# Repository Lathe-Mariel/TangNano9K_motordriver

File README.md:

# TangNano9K_Motordriver Board
  
Tang Nano 9K(Sipeed)用のマザーボード（拡張ボード）です．  
This is mother board for Tang Nano 9K(Sipeed).  

オープンソースの回路CADである，KiCAD のプロジェクトになっています．  
These files were made by KiCAD.
  
/doc ドキュメント用の素材  
/output　KiCADで出力したガーバーデータ  
/output/tangnano9k_motordriver-v3.zip　　PCBメーカにアップロードするファイル  
/sampleProject　この基板向けの数種類のサンプルプロジェクト  

## 機能 Functions
次の機能を実装できます．
- ステッピングモータドライバ x2ch <TB67S101ANG(TOSHIBA)>
- ロータリエンコーダ x2
- 8x8 マトリクスLED <OSL641501-BRA(Optsupply)>
- 7セグメントLED
- DIP Switch(8ch)

You can install these functions with this board.
- Stepper motor driver x2ch
- Rotary encoder x2
- 8x8 Matrix LED
- 7segment LED
- DIP Switch(8ch)

## 電源 Power supply
ボード上にDC-DCコンバータBP5293-50(ROHM)を実装できます．  
DC-DCコンバータには7～26Vを入力し，出力される5VをTang Nano 9Kへ供給できます．  
DC-DC converter can be installed on the board.  
  
基板上のDCジャックへ入力された電圧は，上記DC-DCコンバータとモータ・ドライバICのモータ電源（VM）へ入力されます．  
 
## FPGA側のピンを共用する機能 Multi purpose pins for board functions
　FPGAのピン数が限られているので，拡張ボードの持つ機能のうち，一部の機能は同時利用はできません．  
   
### HDMIコネクタとマトリクスLED＆ロータリ・エンコーダ×2
　DVI信号を出力する場合， `HDMI_CK_N(68)` ， `HDMI_CK_P(69)` ， `HDMI_D0` ～ `HDMI_D2` など8本の信号を使います．これらは，ロータリ・エンコーダ2ch目およびマトリクスLEDの信号と競合します．従ってDVI出力する場合は，ロータリ・エンコーダの2ch目とマトリクスLEDが使えません．  
  ボードにマトリクスLEDを実装するときは，必要に応じて脱着できるようにピンソケット経由にするのがお勧めです． 

### HDMIコネクタとマトリクスLED
　一部の信号を共有しています．HDMIコネクタから信号を出す場合はマトリクスLEDを取り付けない方がよいでしょう．  
 マトリクスLEDを実装するときは，ピンソケットを介して取り付けるのがお勧めです．そうすれば，マトリクスLEDを必要に応じて脱着できます．  
  
### 排他利用する機能の選択 Selection of exclusive functions
　モータドライバの励磁モード選択は `INA1` ， `INA2` ， `INB1` ， `INB2` 端子で行います．  
　2CH目（基板下側）のモータドライバは，ソルダジャンパ `JP1～JP4` をショートすると， `INA1～INB2` の全てがVCCに接続され，励磁モードが2相励磁に固定されます（この場合， `JP5～JP8` はオープンのままにする）．   
 　2ch目のモータドライバで1-2相励磁やW1-2相励磁を行いたい場合，ソルダジャンパ `JP5～JP8` をショートさせます．すると `INA1～INB2` がFPGAに接続されるので，FPGAからHi/Lowを制御できます．  
  　ちなみに1ch目のモータドライバについては，このようなソルダジャンパはありません． `INA1～INB2` は全てFPGAに直結されているので，どの様な励磁モードを使う場合でも，FPGAから制御する必要があります．  
  
  FPGA側では，これらの端子をロータリエンコーダの2ch目と共有しています．  
  従って，モータドライバの2ch目の1-2相励磁選択と，ロータリエンコーダの2ch目は排他利用となります．  
#### 設定例
　①例えば，モータドライバを1chしか使わない場合は， `JP1～JP8` のソルダジャンパをオープンのまま使用します（7セグLEDを使うなら `JP9` のみショートする）．  
 　②例えば，モータドライバの2ch目を1-2相励磁（あるいはW1-2相励磁）で使いたい場合は， `JP5～JP8` のソルダジャンパをショートします（ `INA1～INB2` がFPGAと直結される）．  
  この場合7セグLEDとロータリエンコーダの2ch目は使用できません（実装もしない方がよいでしょう）．  

- JP1 ～ JP4　　ショートさせるとINA1～INB2をTB67S101ANGのVCCピンと接続
- JP5 ～ JP8　　ショートさせるとFPGAとINA1～INB2を接続
- JP9　　JP5の線を7セグLEDのコモンに接続
- JP10 ～ JP17　　マトリクスLEDに（アノード側）電流制限抵抗を付けない場合は，これらのソルダージャンパをショートさせてください  

## マトリクスLED MatrixLED
　~増幅回路も電流制限抵抗も入れていません．~  
　~ワイルドだろぅ？~  
  電流制限抵抗を入れない場合は，ソルダージャンパ `JP10` ～ `JP17` をジャンパします．
　必要であれば，FPGA側のロジックで絞ってください．  
　特に絞らずに使っていますが，LEDもFPGAも壊れないようです．  
  
  電流制限抵抗を入れる場合は，ソルダージャンパ `JP10` ～ `JP17` はオープンなまま抵抗器を実装します．  
トランジスタなどのパターンは基板にありません．電流を増幅せずに，真面目に計算して電流制限抵抗を入れると，LEDがかなり暗くなるようです．  

### マトリクスLED取り付け向き

## 部品
　思いつく限り列挙．抜けがあるかもしれない．  
 ロータリエンコーダのみ，押しスイッチ付きのものが秋月さんに見当たらなかったので，リストに入っていません．  
 基板の4角には穴が開いています．足としてM3程度のボルト・ナットを用意するとよいでしょう．M3だときついのですが，ねじ込めば入ります．  
 （モータドライブ回路用の部品は1ch分の数量を掲載している）
　ちなみに，秋月さんの店頭に出ていない部品もあります（モータドライバなどは，裏オプションなので，お店の人に言うと裏から出してくれます）．

## 機能の補足 Additional for Functions
### モータドライバTB67S101ANG（TOSHIBA）
　このICへ電流制御用のレファレンス電圧を供給する必要があります．Pinは `VREFA` 及び `VREFB` です．このボードでは `VREFA` と `VREFB` は直結されています．これらとFPGAの `27` （モータドライバch1）が接続されています．FPGAからパルスのデューティで所望の電圧を送って下さい．電圧の平滑化のために，RCフィルタのパターンが実装されています．R7とC8（モータドライバch1）に適当な値のものを実装してください．  
 （RCは，1μFと100kオーム．duty3/8くらいから試してください）  

## サンプルプログラム
   
### PolyphonyMatrix_Clock
`/sampleProject`にマトリクスLEDを使った時計のプロジェクトが入っています．  
このプロジェクトはPythonベースの高位合成ツールPolyphonyを利用しています．  
　Gowin EDAのプロジェクトになっているので，そのままGowin EDAで読み込めます．impl/pnr/にビットストリームファイルもあるので，合成しなくてもすぐにFlash Programmerで書き込めます．  
 Verilogファイル `LEDMatrixAB_m.v` は，Polyphonyで `LEDMatrix.py` をコンパイルして生成したものです．
 
### MotorDriver
 モータドライバ IC TB67S101ANG(TOSHIBA) を使ってステッピングモータの2相励磁，1－2相励磁，W1-2相励磁ができます． 
 このサンプルプログラムでは，DVI出力もしています．ピンが競合するのでマトリクスLEDは取り外してください．  
#### DVI出力
　DVI出力については，Interface誌2022年12月号　別冊付録Gowin　の応用編第3章の記事で紹介されたデザインをパクり，一部を改変しています（SPDXライセンス）．  

### Parallel
　回路を複数のモジュールに分けて並列に実行させるサンプルです．3つのLEDを3つの回路で点滅させています．  
  
 （1）TB67S101ANGデータシート  
 https://toshiba.semicon-storage.com/jp/semiconductor/product/motor-driver-ics/stepping-motor-driver-ics/detail.TB67S101ANG.html

# Schematics
https://kicanvas.org/?github=https%3A%2F%2Fgithub.com%2FLathe-Mariel%2FTangNano9K_motordriver%2Ftree%2Fmain

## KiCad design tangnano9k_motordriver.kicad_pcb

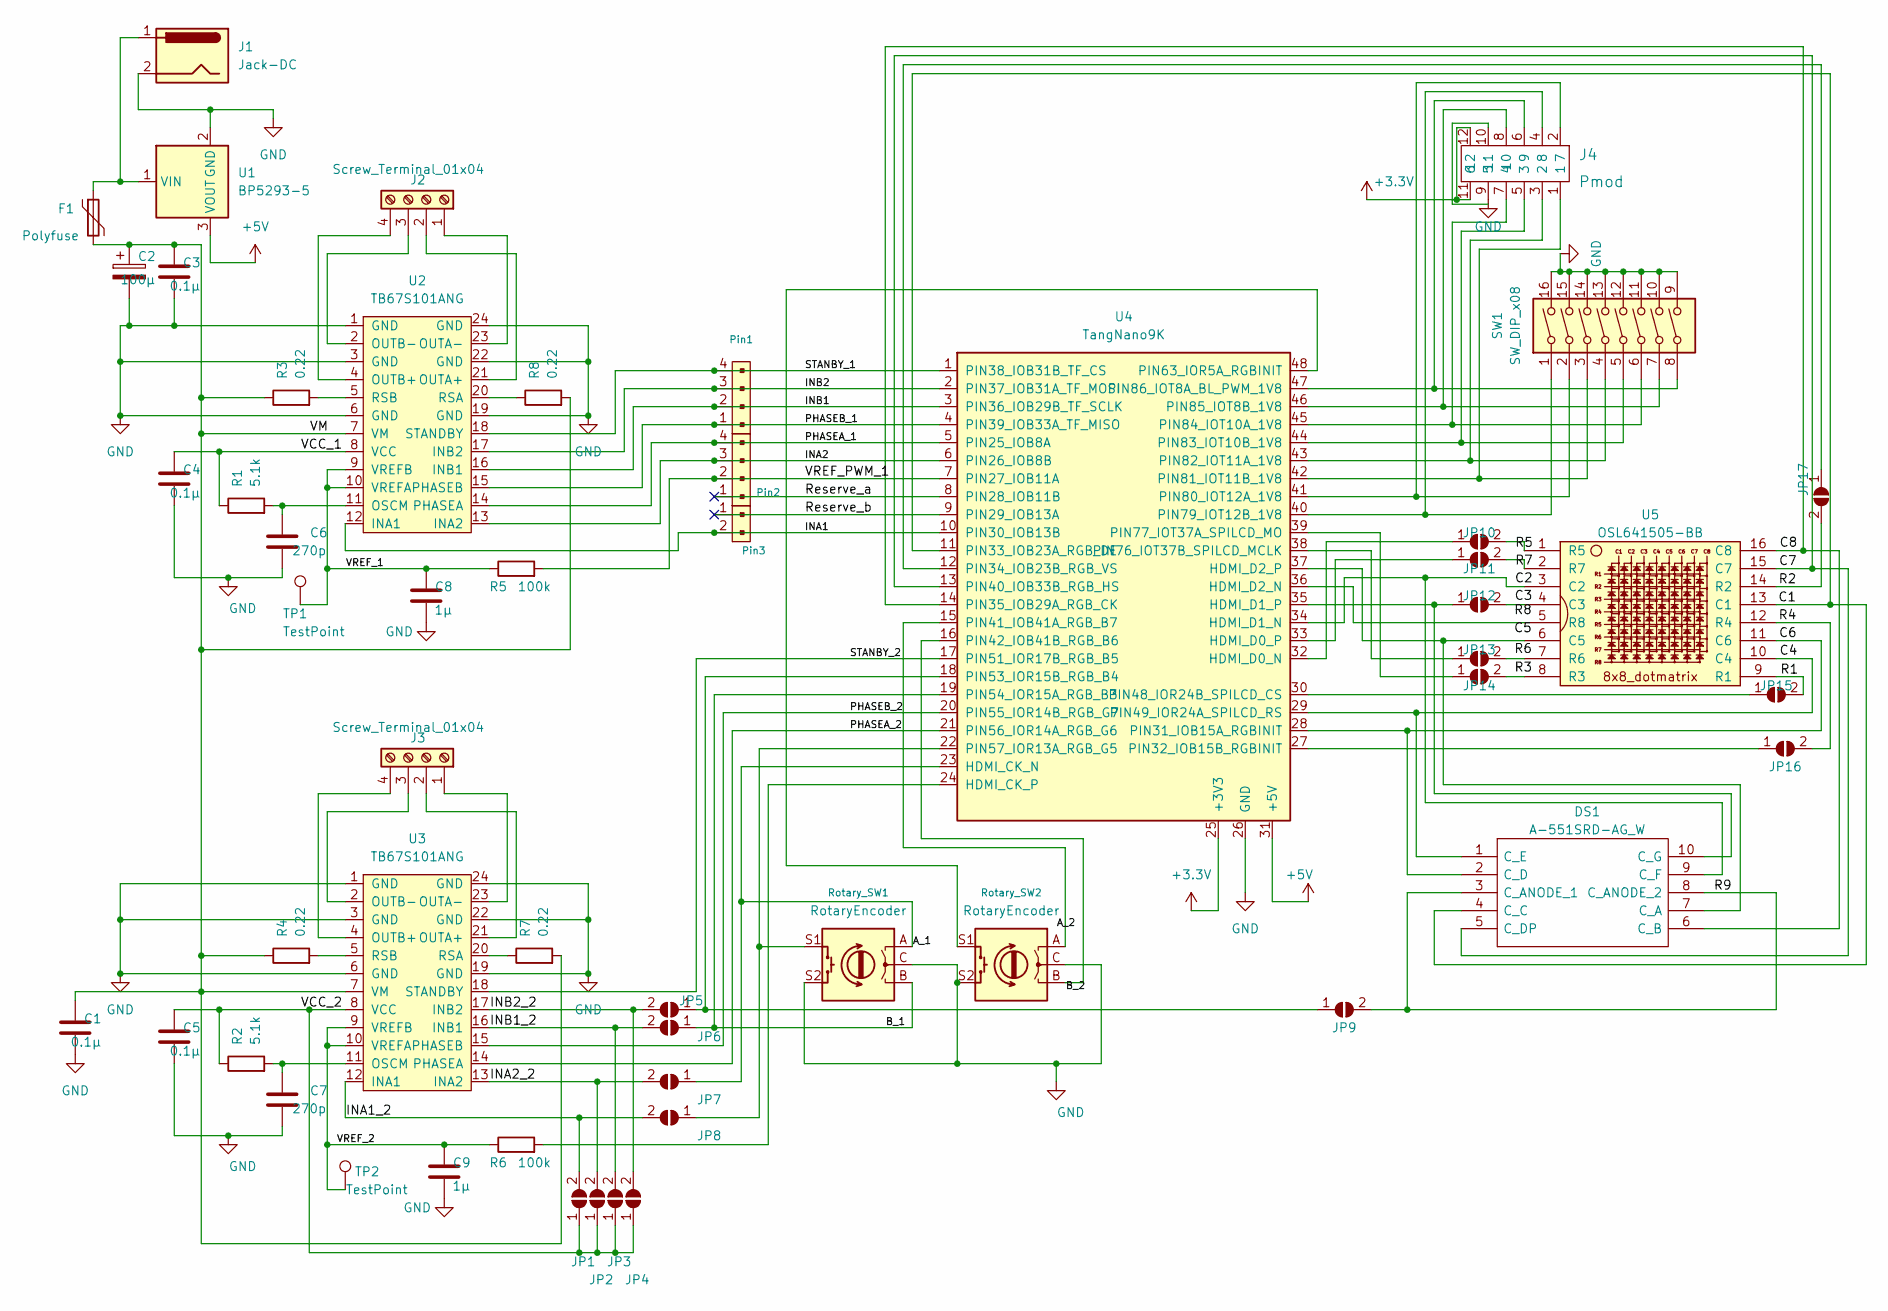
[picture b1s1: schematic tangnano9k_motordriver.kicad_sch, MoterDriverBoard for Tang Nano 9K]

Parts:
C1, C3, C4, C5: 0.1μ; C_Disc_D5.0mm_W2.5mm_P2.50mm
C2: 100μ; CP_Radial_D8.0mm_P2.50mm
C6, C7: 270p; C_Disc_D3.8mm_W2.6mm_P2.50mm
C8, C9: 1μ; C_Disc_D5.0mm_W2.5mm_P2.50mm
DS1: A-551SRD-AG_W; DIPS1524W51P254L1270H825Q10N; Manufacturer_Part_Number A-551SRD-AG/W
F1: Polyfuse; Fuse_Bourns_MF-RHT300
J1: Jack-DC; BarrelJack_Horizontal
J2, J3: Screw_Terminal_01x04; TerminalBlock_bornier-4_P5.08mm
J4: Pmod; PinSocket_2x06_P2.54mm_Horizontal; MPN 67996-412HLF; Digi-Key_PN 609-3219-ND
JP1, JP2, JP3, JP4, JP5, JP6, JP7, JP8, JP9: SolderJumper_2_Open; SolderJumper-2_P1.3mm_Open_TrianglePad1.0x1.5mm
JP10, JP11, JP12, JP13, JP14: SolderJumper_2_Open; SolderJumper_Register_Horizontal
JP15, JP16, JP17: SolderJumper_2_Open; SolderJumper_Register
Pin1, Pin2: Reserve; PinHeader_1x04_P2.54mm_Vertical
Pin3: Reserve; PinHeader_1x02_P2.54mm_Vertical
R1, R2: 5.1k; R_Axial_DIN0207_L6.3mm_D2.5mm_P7.62mm_Horizontal
R3, R4, R7, R8: 0.22; R_Axial_DIN0516_L15.5mm_D5.0mm_P20.32mm_Horizontal
R5, R6: 100k; R_Axial_DIN0207_L6.3mm_D2.5mm_P7.62mm_Horizontal
Rotary_SW1, Rotary_SW2: RotaryEncoder; RotaryEncoder_Alps_EC11E-Switch_Vertical_H20mm
SW1: SW_DIP_x08; SW_DIP_SPSTx08_Slide_9.78x22.5mm_W7.62mm_P2.54mm
TP1: TestPoint; TestPoint_THTPad_1.5x1.5mm_Drill0.7mm
TP2: TestPoint; TestPoint_Pad_1.5x1.5mm
U1: BP5293-5; PinHeader_1x03_P2.54mm_Vertical
U2, U3: TB67S101ANG
U4: TangNano9K; Tang_Nano_9K
U5: OSL641505-BB; OSL641501-ARA

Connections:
+3.3V: J4.11 (6), J4.12, U4.25 (+3V3)
+5V: U1.3 (VOUT), U4.31 (+5V)
/A_1: JP7.1 (A), Rotary_SW1.A, U4.23 (HDMI_CK_N)
/B_1: JP6.1 (A), Rotary_SW1.B, U4.19 (PIN54_IOR15A_RGB_B3)
/INA1: Pin3.2, U2.12 (INA1), U4.10 (PIN30_IOB13B)
/INA1_2: JP1.2 (B), JP8.2 (B), U3.12 (INA1)
/INA2: Pin2.3, U2.13 (INA2), U4.6 (PIN26_IOB8B)
/INA2_2: JP2.2 (B), JP7.2 (B), U3.13 (INA2)
/INB1: Pin1.2, U2.16 (INB1), U4.3 (PIN36_IOB29B_TF_SCLK)
/INB1_2: JP3.2 (B), JP6.2 (B), U3.16 (INB1)
/INB2: Pin1.3, U2.17 (INB2), U4.2 (PIN37_IOB31A_TF_MOSI)
/INB2_2: JP4.2 (B), JP5.2 (B), U3.17 (INB2)
/PHASEA_1: Pin2.4, U2.14 (PHASEA), U4.5 (PIN25_IOB8A)
/PHASEA_2: U3.14 (PHASEA), U4.21 (PIN56_IOR14A_RGB_G6)
/PHASEB_1: Pin1.1, U2.15 (PHASEB), U4.4 (PIN39_IOB33A_TF_MISO)
/PHASEB_2: U3.15 (PHASEB), U4.20 (PIN55_IOR14B_RGB_G7)
/R1: JP15.2 (B), U5.9 (R1)
/R9: DS1.3 (C_ANODE_1), DS1.8 (C_ANODE_2), JP9.2 (B)
/Reserve_a: Pin2.1, U4.8 (PIN28_IOB11B)
/Reserve_b: Pin3.1, U4.9 (PIN29_IOB13A)
/STANBY_1: Pin1.4, U2.18 (STANDBY), U4.1 (PIN38_IOB31B_TF_CS)
/STANBY_2: U3.18 (STANDBY), U4.17 (PIN51_IOR17B_RGB_B5)
/VCC_1: C4.1, R1.1, U2.8 (VCC)
/VCC_2: C5.1, JP1.1 (A), JP2.1 (A), JP3.1 (A), JP4.1 (A), R2.1, U3.8 (VCC)
/VM: C1.1, C2.1, C3.1, F1.2, R3.1, R4.1, R7.2, R8.2, U2.7 (VM), U3.7 (VM)
/VREF_1: C8.1, R5.1, TP1.1, U2.9 (VREFB), U2.10 (VREFA)
/VREF_2: C9.1, R6.1, TP2.1, U3.9 (VREFB), U3.10 (VREFA)
/VREF_PWM_1: Pin2.2, R5.2, U4.7 (PIN27_IOB11A)
GND: C1.2, C2.2, C3.2, C4.2, C5.2, C6.2, C7.2, C8.2, C9.2, J1.2, J4.9 (5), Rotary_SW1.C, Rotary_SW1.S2, Rotary_SW2.C, Rotary_SW2.S2, SW1.9, SW1.10, SW1.11, SW1.12, SW1.13, SW1.14, SW1.15, SW1.16, U1.2 (GND), U2.1 (GND), U2.3 (GND), U2.6 (GND), U2.19 (GND), U2.22 (GND), U2.24 (GND), U3.1 (GND), U3.3 (GND), U3.6 (GND), U3.19 (GND), U3.22 (GND), U3.24 (GND), U4.26 (GND)
unnamed: C6.1, R1.2, U2.11 (OSCM)
unnamed: C7.1, R2.2, U3.11 (OSCM)
unnamed: DS1.1 (C_E), U4.29 (PIN49_IOR24A_SPILCD_RS), U5.10 (C4)
unnamed: DS1.2 (C_D), U4.28 (PIN31_IOB15A_RGBINIT), U5.11 (C6)
unnamed: DS1.4 (C_C), U4.11 (PIN33_IOB23A_RGB_DE), U5.13 (C1)
unnamed: DS1.5 (C_DP), U4.13 (PIN40_IOB33B_RGB_HS), U5.15 (C7)
unnamed: DS1.6 (C_B), U4.14 (PIN35_IOB29A_RGB_CK), U5.16 (C8)
unnamed: DS1.7 (C_A), U4.37 (HDMI_D2_P), U5.6 (C5)
unnamed: DS1.9 (C_F), U4.34 (HDMI_D1_N), U5.3 (C2)
unnamed: DS1.10 (C_G), JP12.1 (A), U4.35 (HDMI_D1_P)
unnamed: F1.1, J1.1, U1.1 (VIN)
unnamed: J2.1, U2.23 (OUTA-)
unnamed: J2.2, U2.21 (OUTA+)
unnamed: J2.3, U2.2 (OUTB-)
unnamed: J2.4, U2.4 (OUTB+)
unnamed: J3.1, U3.23 (OUTA-)
unnamed: J3.2, U3.21 (OUTA+)
unnamed: J3.3, U3.2 (OUTB-)
unnamed: J3.4, U3.4 (OUTB+)
unnamed: JP5.1 (A), JP9.1 (A), U4.18 (PIN53_IOR15B_RGB_B4)
unnamed: JP8.1 (A), Rotary_SW1.S1, U4.22 (PIN57_IOR13A_RGB_G5)
unnamed: JP10.1 (A), U4.32 (HDMI_D0_N)
unnamed: JP10.2 (B), U5.1 (R5)
unnamed: JP11.1 (A), U4.33 (HDMI_D0_P)
unnamed: JP11.2 (B), U5.2 (R7)
unnamed: JP12.2 (B), U5.4 (C3)
unnamed: JP13.1 (A), U4.38 (PIN76_IOT37B_SPILCD_MCLK)
unnamed: JP13.2 (B), U5.7 (R6)
unnamed: JP14.1 (A), U4.39 (PIN77_IOT37A_SPILCD_MO)
unnamed: JP14.2 (B), U5.8 (R3)
unnamed: JP15.1 (A), U4.30 (PIN48_IOR24B_SPILCD_CS)
unnamed: JP16.1 (A), U4.27 (PIN32_IOB15B_RGBINIT)
unnamed: JP16.2 (B), U5.12 (R4)
unnamed: JP17.1 (A), U4.12 (PIN34_IOB23B_RGB_VS)
unnamed: JP17.2 (B), U5.14 (R2)
unnamed: R3.2, U2.5 (RSB)
unnamed: R4.2, U3.5 (RSB)
unnamed: R6.2, U4.24 (HDMI_CK_P)
unnamed: R7.1, U3.20 (RSA)
unnamed: R8.1, U2.20 (RSA)
unnamed: Rotary_SW2.A, U4.15 (PIN41_IOB41A_RGB_B7)
unnamed: Rotary_SW2.B, U4.16 (PIN42_IOB41B_RGB_B6)
unnamed: Rotary_SW2.S1, U4.48 (PIN63_IOR5A_RGBINIT)
unnamed: J4.4 (8), SW1.1, U4.40 (PIN79_IOT12B_1V8)
unnamed: J4.2 (7), SW1.2, U4.41 (PIN80_IOT12A_1V8)
unnamed: J4.1, SW1.3, U4.42 (PIN81_IOT11B_1V8)
unnamed: J4.3 (2), SW1.4, U4.43 (PIN82_IOT11A_1V8)
unnamed: J4.5 (3), SW1.5, U4.44 (PIN83_IOT10B_1V8)
unnamed: J4.7 (4), SW1.6, U4.45 (PIN84_IOT10A_1V8)
unnamed: J4.8 (10), SW1.7, U4.46 (PIN85_IOT8B_1V8)
unnamed: J4.6 (9), SW1.8, U4.47 (PIN86_IOT8A_BL_PWM_1V8)
unnamed: U4.36 (HDMI_D2_N), U5.5 (R8)

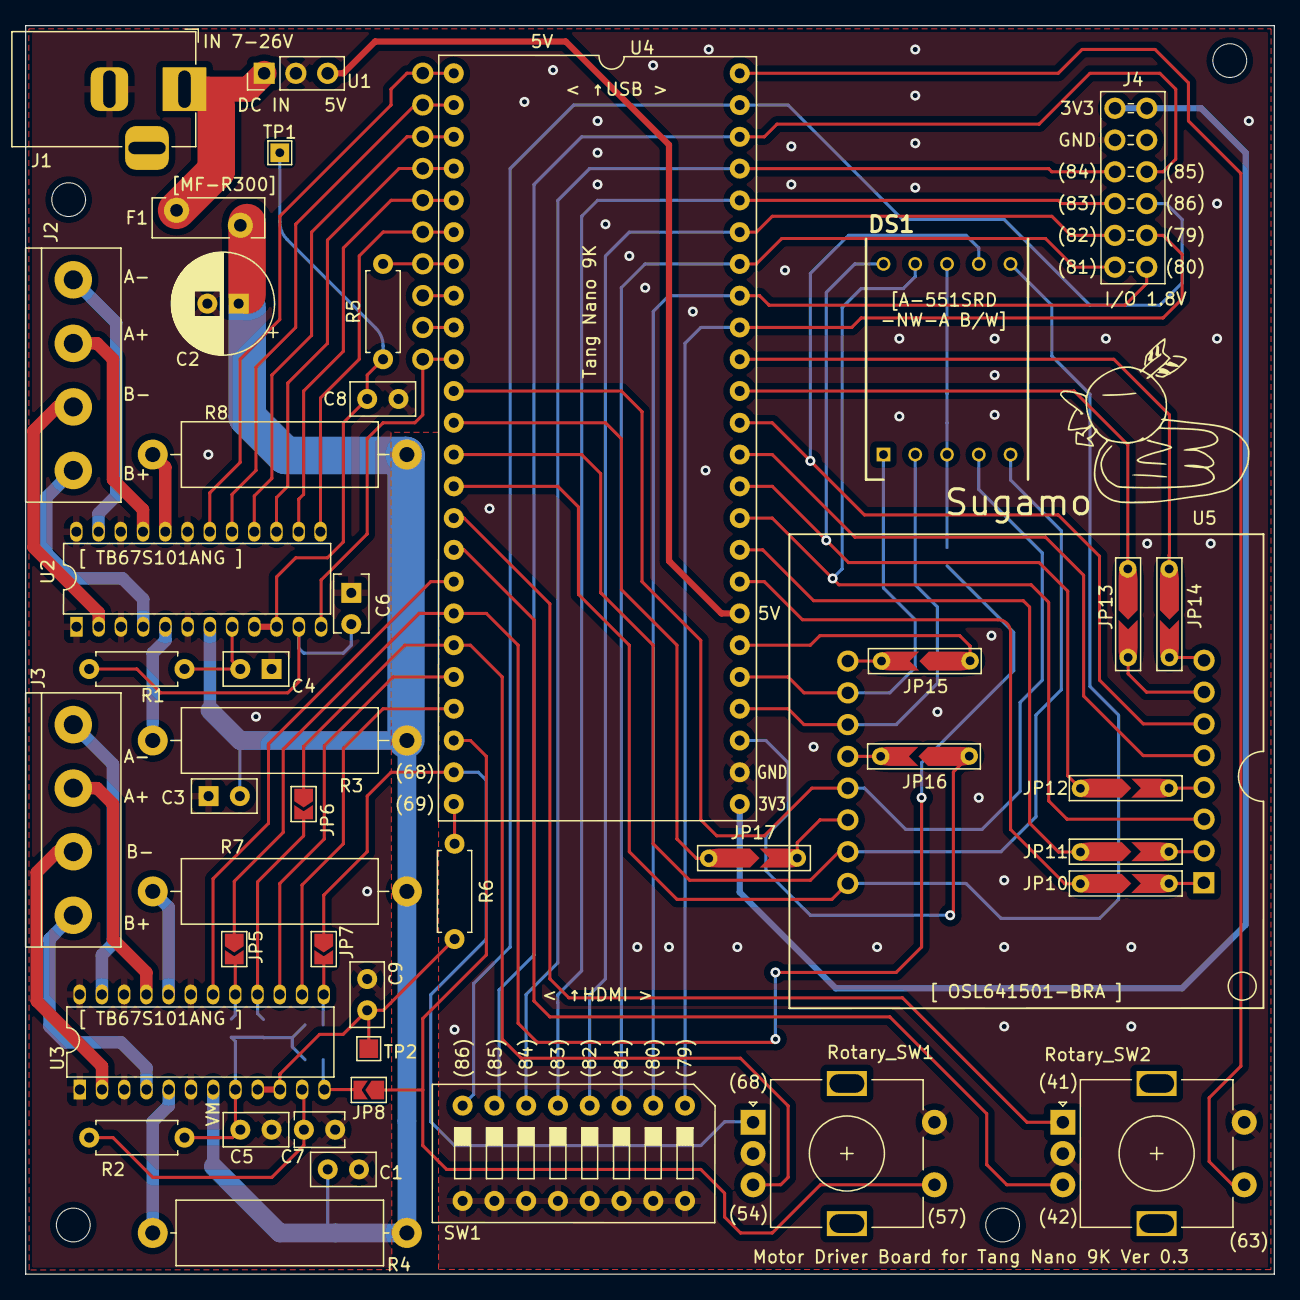
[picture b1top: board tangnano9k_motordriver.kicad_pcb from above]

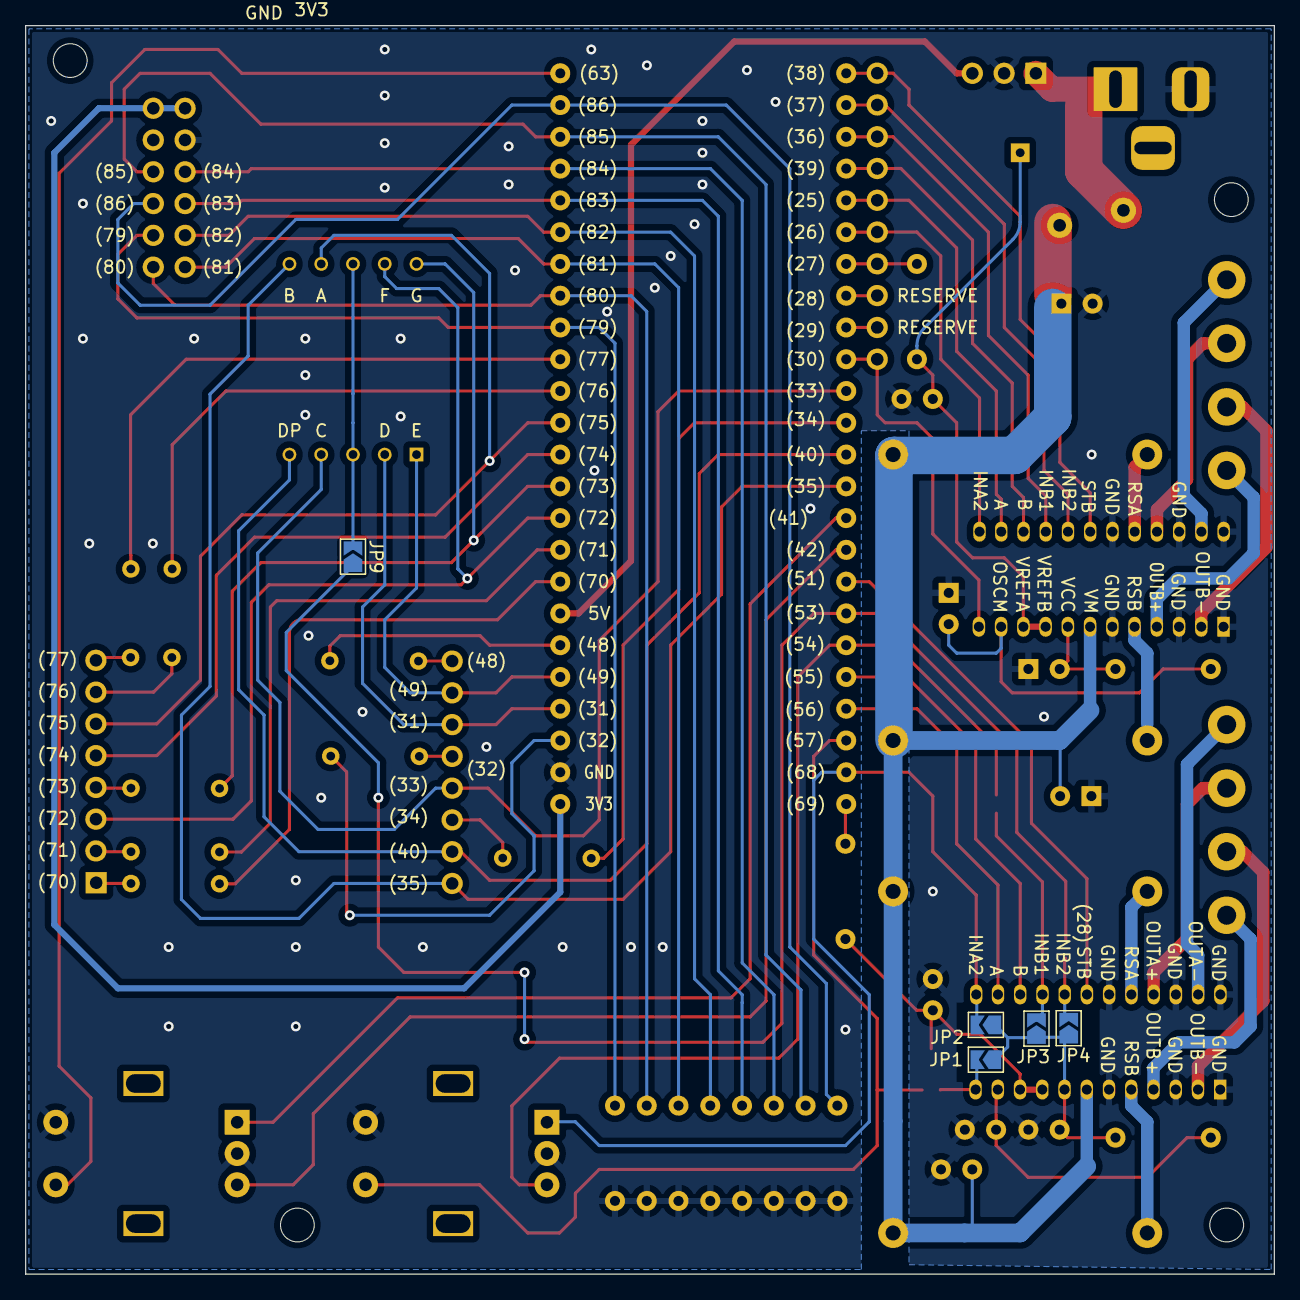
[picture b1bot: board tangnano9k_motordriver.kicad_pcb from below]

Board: 2 copper layers, 99.8 x 99.8 mm, 53 parts (5 on the bottom side), 81 nets.

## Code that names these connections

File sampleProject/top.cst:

//Copyright (C)2014-2022 Gowin Semiconductor Corporation.
//All rights reserved.
//File Title: Physical Constraints file
//GOWIN Version: 1.9.8.03 Education
//Part Number: GW1NR-LV9QN88PC6/I5
//Device: GW1NR-9C
//Created Time: Thu 09 08 15:53:57 2022

IO_LOC "ch1_phase_a" 25;
IO_PORT "ch1_phase_a" IO_TYPE=LVCMOS33 PULL_MODE=UP DRIVE=8;
IO_LOC "ch1_phase_b" 39;
IO_PORT "ch1_phase_b" IO_TYPE=LVCMOS33 PULL_MODE=UP DRIVE=8;
IO_LOC "ch1_INB1" 36;
IO_PORT "ch1_INB1" IO_TYPE=LVCMOS33 PULL_MODE=UP DRIVE=8;
IO_LOC "ch1_INB2" 37;
IO_PORT "ch1_INB2" IO_TYPE=LVCMOS33 PULL_MODE=UP DRIVE=8;
IO_LOC "ch1_INA1" 30;
IO_PORT "ch1_INA1" IO_TYPE=LVCMOS33 PULL_MODE=UP DRIVE=8;
IO_LOC "ch1_INA2" 26;
IO_PORT "ch1_INA2" IO_TYPE=LVCMOS33 PULL_MODE=UP DRIVE=8;
IO_LOC "ch1_STANBY" 38;
IO_PORT "ch1_STANBY" IO_TYPE=LVCMOS33 PULL_MODE=UP DRIVE=8;
IO_LOC "ch1_VREF" 27;
IO_PORT "ch1_VREF" IO_TYPE=LVCMOS33 PULL_MODE=UP DRIVE=8;
/*
IO_LOC "2_phase_a" 55;
IO_PORT "2_phase_a" IO_TYPE=LVCMOS33 PULL_MODE=UP DRIVE=8;
IO_LOC "2_phase_b" 56;
IO_PORT "2_phase_b" IO_TYPE=LVCMOS33 PULL_MODE=UP DRIVE=8;
IO_LOC "2_INB1" 54;  //exclusive
IO_PORT "2_INB1" IO_TYPE=LVCMOS33 PULL_MODE=UP DRIVE=8;
IO_LOC "2_INB2" 53;  //exclusive
IO_PORT "2_INB2" IO_TYPE=LVCMOS33 PULL_MODE=UP DRIVE=8;
IO_LOC "2_INA1" 57;  //exclusive
IO_PORT "2_INA1" IO_TYPE=LVCMOS33 PULL_MODE=UP DRIVE=8;
IO_LOC "2_INA2" 68;  //exclusive
IO_PORT "2_INA2" IO_TYPE=LVCMOS33 PULL_MODE=UP DRIVE=8;
IO_LOC "2_STANBY" 51;
IO_PORT "2_STANBY" IO_TYPE=LVCMOS33 PULL_MODE=UP DRIVE=8;
IO_LOC "2_VREF" 69;
IO_PORT "2_VREF" IO_TYPE=LVCMOS33 PULL_MODE=UP DRIVE=8;
*/

IO_LOC "scl" 28;
IO_PORT "scl" IO_TYPE=LVCMOS33 PULL_MODE=UP DRIVE=8 OPEN_DRAIN=ON;
IO_LOC "sda" 29;
IO_PORT "sda" IO_TYPE=LVCMOS33 PULL_MODE=UP DRIVE=8 OPEN_DRAIN=ON;

/*
IO_LOC "cathode[7]" 35;
IO_PORT "cathode[7]" IO_TYPE=LVCMOS33 PULL_MODE=UP DRIVE=8;
IO_LOC "cathode[6]" 40;
IO_PORT "cathode[6]" IO_TYPE=LVCMOS33 PULL_MODE=UP DRIVE=8;
IO_LOC "cathode[5]" 31;
IO_PORT "cathode[5]" IO_TYPE=LVCMOS33 PULL_MODE=UP DRIVE=8;
IO_LOC "cathode[4]" 75;
IO_PORT "cathode[4]" IO_TYPE=LVCMOS33 PULL_MODE=UP DRIVE=8;
IO_LOC "cathode[3]" 49;
IO_PORT "cathode[3]" IO_TYPE=LVCMOS33 PULL_MODE=UP DRIVE=8;
IO_LOC "cathode[2]" 73;
IO_PORT "cathode[2]" IO_TYPE=LVCMOS33 PULL_MODE=UP DRIVE=8;
IO_LOC "cathode[1]" 72;
IO_PORT "cathode[1]" IO_TYPE=LVCMOS33 PULL_MODE=UP DRIVE=8;
IO_LOC "cathode[0]" 33;
IO_PORT "cathode[0]" IO_TYPE=LVCMOS33 PULL_MODE=UP DRIVE=8;
IO_LOC "anode[7]" 74;
IO_PORT "anode[7]" IO_TYPE=LVCMOS33 PULL_MODE=UP DRIVE=8;
IO_LOC "anode[6]" 71;
IO_PORT "anode[6]" IO_TYPE=LVCMOS33 PULL_MODE=UP DRIVE=8;
IO_LOC "anode[5]" 76;
IO_PORT "anode[5]" IO_TYPE=LVCMOS33 PULL_MODE=UP DRIVE=8;
IO_LOC "anode[4]" 70;
IO_PORT "anode[4]" IO_TYPE=LVCMOS33 PULL_MODE=UP DRIVE=8;
IO_LOC "anode[3]" 32;
IO_PORT "anode[3]" IO_TYPE=LVCMOS33 PULL_MODE=UP DRIVE=8;
IO_LOC "anode[2]" 77;
IO_PORT "anode[2]" IO_TYPE=LVCMOS33 PULL_MODE=UP DRIVE=8;
IO_LOC "anode[1]" 34;
IO_PORT "anode[1]" IO_TYPE=LVCMOS33 PULL_MODE=UP DRIVE=8;
IO_LOC "anode[0]" 48;
IO_PORT "anode[0]" IO_TYPE=LVCMOS33 PULL_MODE=UP DRIVE=8;
*/
IO_LOC "boardLED[0]" 10;
IO_PORT "boardLED[0]" IO_TYPE=LVCMOS18 PULL_MODE=UP DRIVE=8;
IO_LOC "boardLED[1]" 11;
IO_PORT "boardLED[1]" IO_TYPE=LVCMOS18 PULL_MODE=UP DRIVE=8;
IO_LOC "boardLED[2]" 13;
IO_PORT "boardLED[2]" IO_TYPE=LVCMOS18 PULL_MODE=UP DRIVE=8;
IO_LOC "boardLED[3]" 14;
IO_PORT "boardLED[3]" IO_TYPE=LVCMOS18 PULL_MODE=UP DRIVE=8;
IO_LOC "boardLED[4]" 15;
IO_PORT "boardLED[4]" IO_TYPE=LVCMOS18 PULL_MODE=UP DRIVE=8;
IO_LOC "boardLED[5]" 16;
IO_PORT "boardLED[5]" IO_TYPE=LVCMOS18 PULL_MODE=UP DRIVE=8;

IO_LOC "clk" 52;
IO_PORT "clk" IO_TYPE=LVCMOS33 PULL_MODE=UP;
/*
IO_LOC "rotary2_a" 68;  //exclusive
IO_PORT "rotary2_a" IO_TYPE=LVCMOS33 PULL_MODE=UP;
IO_LOC "rotary2_b" 54;  //exclusive
IO_PORT "rotary2_b" IO_TYPE=LVCMOS33 PULL_MODE=UP;
IO_LOC "rotary2_SW" 57;  //exclusive
IO_PORT "rotary2_SW" IO_TYPE=LVCMOS33 PULL_MODE=UP;
IO_LOC "rotary1_SW" 63;
IO_PORT "rotary1_SW" IO_TYPE=LVCMOS33 PULL_MODE=UP;
IO_LOC "rotary1_a" 41;
IO_PORT "rotary1_a" IO_TYPE=LVCMOS33 PULL_MODE=UP;
IO_LOC "rotary1_b" 42;
IO_PORT "rotary1_b" IO_TYPE=LVCMOS33 PULL_MODE=UP;
IO_LOC "sw2" 3;
IO_PORT "sw2" IO_TYPE=LVCMOS18 PULL_MODE=UP;
IO_LOC "sw1" 4;
IO_PORT "sw1" IO_TYPE=LVCMOS18 PULL_MODE=UP;
*/
/*7 //seg LED
IO_LOC "LED7seg_anode" 53;  //exclusive
IO_PORT "LED7seg_anode" IO_TYPE=LVCMOS33 PULL_MODE=UP DRIVE=8;
*/

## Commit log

2023-01-03 ver02
2023-03-14 added dip_sw sample
